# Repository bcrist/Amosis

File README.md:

# Amosis Keyboard

The Amosis is a 40% split keywell board with a Cirque trackpad built into each side.  The case is 3D printed, and features a keywell shape similar to Kinesis or Dactyl keyboards, except with only three rows.

## Controller
This keyboard uses custom controller firmware written from scratch in Zig, and running on an RP2040.

It does not have runtime-swappable layouts or configuration.  Instead, the keyboard layout, layer switching logic, mouse sensitivity, etc. is baked into the firmware, but updating the firmware is just a matter of holding the BOOT button while pressing the RESET button, then dragging a UF2 file to the RPI USB drive.

All of interesting configuration/layout stuff is handed in the [logic.zig](https://github.com/bcrist/Amosis/blob/main/firmware/logic.zig) file.  It should be relatively easy to customize the layout, though if you want to make behavioral changes, you will likely need to know some Zig.

The default layout is based on [Hands Down Gold](https://sites.google.com/alanreiser.com/handsdown#h.j66p50cw2471).  The exact details can be found [here](https://docs.google.com/spreadsheets/d/1Owf2ERAmP1oHp472hNBu8RwOKwRJ6sjyrHRkhDTo6_Y/edit?usp=sharing).

It would probably be possible to use something like QMK with Amosis controllers, but please don't ask me to help with that; I have no interest and little experience with QMK, ZMK, etc.

## Trackpad
Each side of the keyboard integrates a 40mm Cirque GlidePoint trackpad from a Steam Controller.  While Valve stopped producing Steam Controllers years ago, you can still purchase the trackpads from [Mouser](https://www.mouser.com/c/?marcom=118816186), but you will likely need to make some modifications to make this work:

* There are several sizes available; the Steam Controller uses the largest 40mm size (TM40040), but you could use a smaller one if you adjust the case design.
* The retail Circues offer several options for plastic overlays, but the Steam Controller used custom overlays, so you may need to adjust the case design for your chosen overlay style.
* There are (or were) both SPI and I2C versions available.  The Steam Controller only uses SPI, so you'll need to adjust the firmware if you want to use an I2C version (though I think you can change it just by adding/removing a resistor on the Cirque board).  The SPI versions have part numbers TMxx0xx-2024 while the I2C versions have part numbers TMxx0xx-2023.  At time of writing, it appears Mouser no longer carries the I2C version.
* The Steam Controller uses a customized connector pinout that's different than what's documented in the datasheet for the retail version.  You'll need to adjust the schematic board layout to accomodate this.
* An [Alps Haptic Reactor](https://www.mouser.com/ProductDetail/Alps-Alpine/AFT14A903A) force-feedback element is glued to the back of the Steam Controller version and its power is routed through the same FFC cable.  If you buy this separately, you'll have to figure out how you want to connect it to the board.

## Building

Have the controller boards manufactured using the files in the `kicad/gerbers/left/` and `kicad/gerbers/right` folders.

Ensure dependencies are available on your path:
* [Zig](https://ziglang.org/download/)
* [OpenSCAD](https://openscad.org/downloads.html) (2023.03.18 or newer; scroll down to "Development Snapshots")

Adjust the keymapping and layer logic as you like, then run `zig build`.

3D print a case using `zig-out/bin/left.stl` and `zig-out/bin/right.stl`.

Flash the `zig-out/bin/firmware.uf2` and to both controllers (the same file can be used for both sides because the firmware will detect which side it is at boot).

### Wiring
The 3 row signals are driven to 3.3V when scanning a row, and 0V when not scanning that row.
The 7 column signals are read as inputs with weak pull-downs, and treat a high value as indicating that a switch is pressed.
Therefore, there are 2 possible ways to wire the diode/switch matrix that will work:
* Diodes between the row signals and the switches, with a common anode for each row.
* Diodes between the column signals and the switches, with a common cathode for each column.

Note the line on diode packages indicates the cathode side.
Also note while the schematics list a schottky diode part number, any general purpose diodes will work fine for the matrix, e.g. 1N914/1N4148, 1N4001, etc.

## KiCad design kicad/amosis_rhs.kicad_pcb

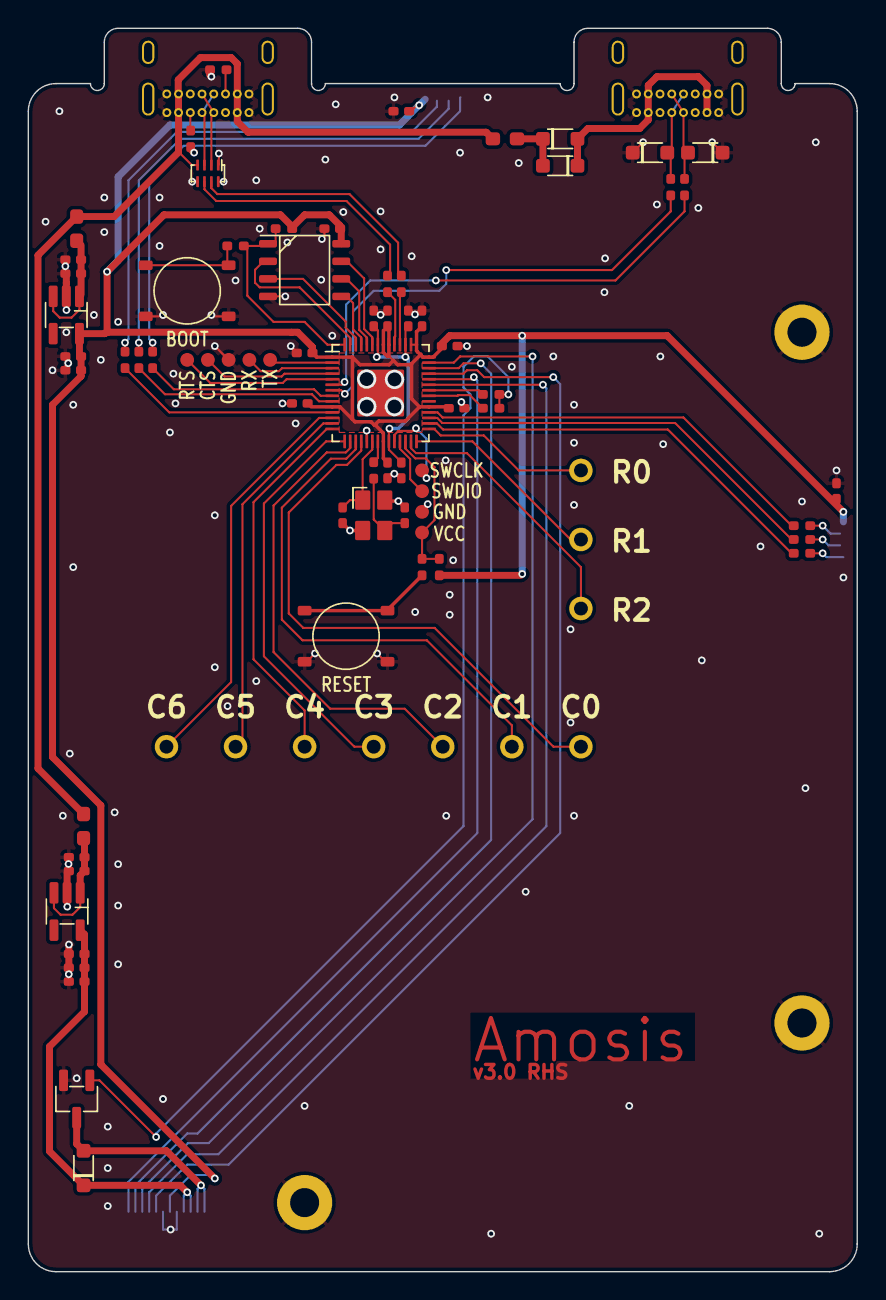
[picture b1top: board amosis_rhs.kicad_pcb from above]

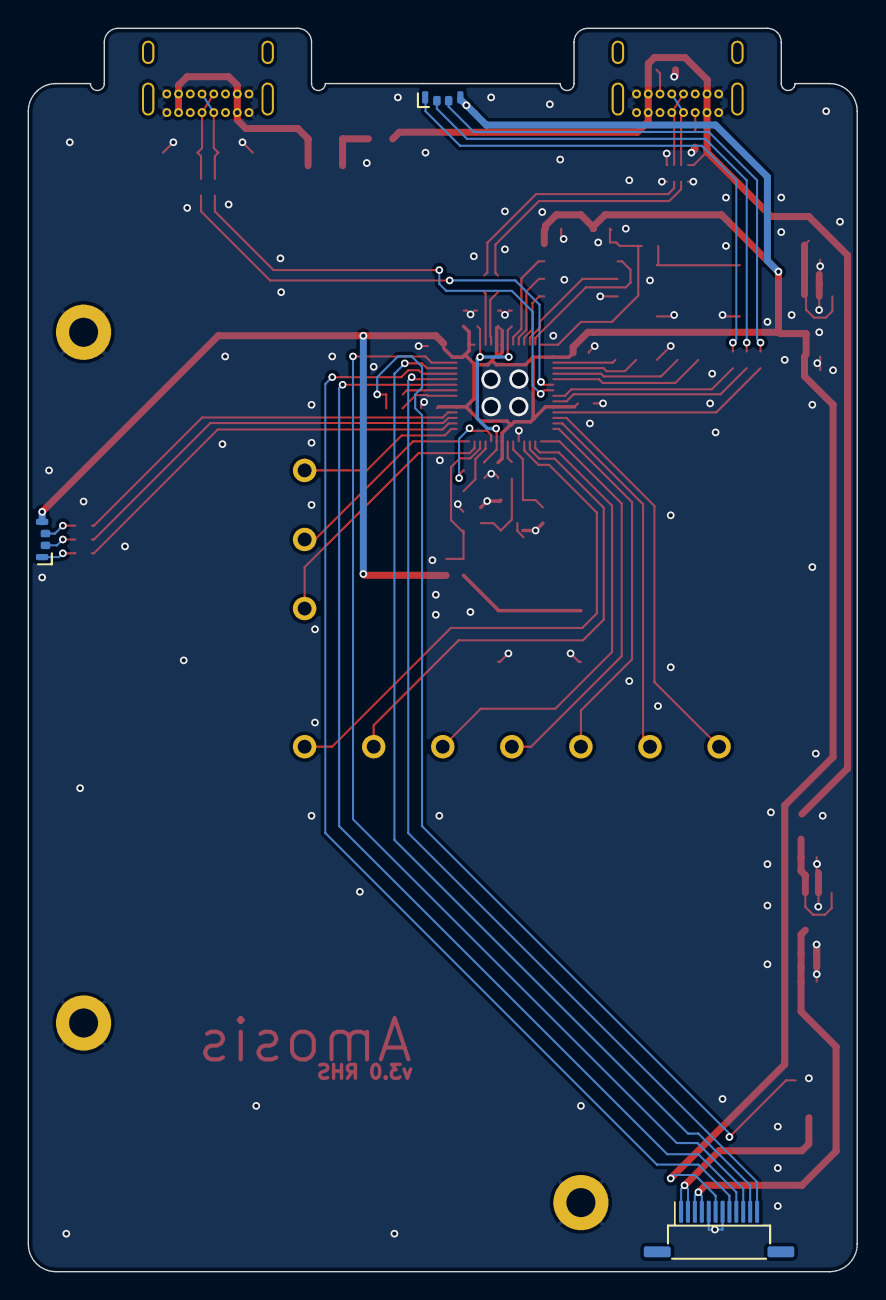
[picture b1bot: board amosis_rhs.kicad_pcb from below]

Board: 2 copper layers, 60.0 x 90.0 mm, 87 parts (5 on the bottom side), 70 nets.

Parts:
C1, C4, C5, C8, C10, C17: 1; C_0402
C2, C3, C6, C7, C11, C12, C13, C14, C15, C16, C18, C19, C20, C23, C24: 0.1; C_0402
C9: 10; C_0402
C21, C22: 14p; C_0402
COL_{0}1: COL_{0}; PinHeader_1x01
COL_{1}1: COL_{1}; PinHeader_1x01
COL_{2}1: COL_{2}; PinHeader_1x01
COL_{3}1: COL_{3}; PinHeader_1x01
COL_{4}1: COL_{4}; PinHeader_1x01
COL_{5}1: COL_{5}; PinHeader_1x01
COL_{6}1: ROW_{0}; PinHeader_1x01
D22, D23: CUS520; SOD-323
D24: ECMF02-4CMX8; DFN-8-2.5x1.2-P0.45
D25, D26: DESD5V0U1BA; SOD-323
D27, D28: LED_BGRA; Harvatek-B3233GBR-20
D29: MMBD914LT1; SOD-323
FB1, FB2, FB3: PE-0603FB121ST; L_0603
J1, J2: USB-C-16; USB_GCT_USB4085-FG-A
J3: VALVE; FFC_GCT_FFC2B28-12-G
M1, M2, M3: GND; MountingHole_M2_Pad
Q1: MMBT3904; SOT-23
R1, R13: 10K; R_0402
R2, R12, R16: 1K; R_0402
R3, R4: 50; R_0402
R5, R8: 27.4; R_0402
R6, R7, R18: 5.1K; R_0402
R9, R14: 120; R_0402
R10, R11, R15, R17: 10; R_0402
R19: 2.2K; R_0402
ROW_{0}1: ROW_{1}; PinHeader_1x01
ROW_{1}1: ROW_{2}; PinHeader_1x01
ROW_{2}1: ROW_{3}; PinHeader_1x01
SW22: RESET; SW_CK_PTS526
SW23: BOOT; SW_CK_PTS526
U1: MIC5504-3.3YM5; SOT-23-5
U2: MIC5504-2.5YM5; SOT-23-5
U3: RP2040; QFN-56-EP-7x7-P0.4
U4: ZD25Q80CT; SOP-8-4.9x3.9-P1.27
X1: RH100-12.000-12-1010-X-TR-NS2
tCTS1: CTS; TestPoint
tGND1, tGND2: GND; TestPoint
tRTS1: RTS; TestPoint
tRUN1: VCC; TestPoint
tRX1: RX; TestPoint
tSWCLK1: SWCLK; TestPoint
tSWDIO1: SWDIO; TestPoint
tTX1: TX; TestPoint

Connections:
+2V5: C7.1, C8.1, C9.1, D29.1 (K), J3.3, J3.4, U2.5 (VOUT)
/COL_{0}: COL_{0}1.1, U3.18 (P15)
/COL_{1}: COL_{1}1.1, U3.17 (P14)
/COL_{2}: COL_{2}1.1, U3.16 (P13)
/COL_{3}: COL_{3}1.1, U3.15 (P12)
/COL_{4}: COL_{4}1.1, U3.14 (P11)
/COL_{5}: COL_{5}1.1, U3.13 (P10)
/COL_{6}: COL_{6}1.1, U3.12 (P9)
/DR: J3.9, U3.37 (P25)
/LINK_RX: R3.2, U3.7 (P5)
/LINK_TX: R4.1, U3.6 (P4)
/MISO: J3.11, U3.40 (P28/A2)
/MOSI: J3.8, U3.39 (P27/A1)
/ROW_{0}: ROW_{0}1.1, U3.29 (P18)
/ROW_{1}: ROW_{1}1.1, U3.28 (P17)
/ROW_{2}: ROW_{2}1.1, U3.27 (P16)
/SCLK: J3.12, U3.38 (P26/A0)
/SS: J3.10, U3.41 (P29/A3)
GND: C1.2, C2.2, C3.2, C4.2, C5.2, C6.2, C7.2, C8.2, C9.2, C10.2, C11.2, C12.2, C13.2, C14.2, C15.2, C16.2, C17.2, C18.2, C19.2, C20.2, C21.2, C22.2, C23.2, C24.2, D24.1, D24.5, D24.8, D25.1 (A1), D26.1 (A1), J1.A1 (GND), J1.A12 (GND), J1.B1 (GND), J1.B12 (GND), J2.A1 (GND), J2.A12 (GND), J2.B1 (GND), J2.B12 (GND), J3.5, J3.7, M1.1, M2.1, M3.1, Q1.2 (E), R6.2, R7.2, SW22.3, SW22.4, SW23.3, SW23.4, U1.2 (GND), U2.2 (GND), U3.19 (GND), U3.EP (GND), U4.4 (GND), X1.2, X1.4, tGND1.1, tGND2.1
unnamed: C22.1, R12.2, X1.3
unnamed: D22.2 (A), D23.1 (K), FB3.2
unnamed: D22.1 (K), D23.2 (A), J1.A4 (V_{BUS}), J1.A9 (V_{BUS}), J1.B4 (V_{BUS}), J1.B9 (V_{BUS})
unnamed: D24.6, R5.2
unnamed: D24.7, R8.1
unnamed: D25.2 (A2), J1.A6 (D+1), J1.B6 (D+2), R3.1
unnamed: D26.2 (A2), J1.A7 (D-1), J1.B7 (D-2), R4.2
unnamed: D27.1 (BK), R9.2
unnamed: D27.2 (GK), R10.2
unnamed: D27.3 (RK), R11.2
unnamed: D28.1 (BK), R14.2
unnamed: D28.2 (GK), R15.2
unnamed: D28.3 (RK), R17.2
unnamed: D29.2 (A), J3.1, J3.2, Q1.3 (C)
unnamed: J2.A5 (CC1), R6.1
unnamed: J2.B5 (CC2), R7.1
unnamed: D24.3, J2.A6 (D+1), J2.B6 (D+2)
unnamed: D24.2, J2.A7 (D-1), J2.B7 (D-2)
unnamed: Q1.1 (B), R18.2, R19.2
unnamed: R2.2, SW22.1, SW22.2
unnamed: R16.2, SW23.1, SW23.2
unnamed: C1.1, C2.1, FB1.2, U1.1 (VIN), U1.3 (EN)
unnamed: C5.1, C6.1, FB2.2, U2.1 (VIN), U2.3 (EN)
unnamed: U3.2 (P0), tTX1.1
unnamed: U3.3 (P1), tRX1.1
unnamed: U3.4 (P2), tCTS1.1
unnamed: U3.5 (P3), tRTS1.1
unnamed: R9.1, U3.8 (P6)
unnamed: R10.1, U3.9 (P7)
unnamed: R11.1, U3.11 (P8)
unnamed: R14.1, U3.30 (P19)
unnamed: R15.1, U3.31 (P20)
unnamed: R17.1, U3.32 (P21)
unnamed: R18.1, U3.35 (P23)
unnamed: R19.1, U3.36 (P24)
unnamed: U3.52 (QSPI_{CLK}), U4.6 (CLK)
unnamed: U3.53 (QSPI_{SD0}), U4.5 (D0)
unnamed: U3.55 (QSPI_{SD1}), U4.2 (D1)
unnamed: U3.54 (QSPI_{SD2}), U4.3 (D2)
unnamed: U3.51 (QSPI_{SD3}), U4.7 (D3)
unnamed: R13.2, R16.1, U3.56 (QSPI_{~SS}), U4.1 (~CS)
unnamed: R1.2, R2.1, U3.26 (RUN), tRUN1.1
unnamed: U3.24 (SWCLK), tSWCLK1.1
unnamed: U3.25 (SWDIO), tSWDIO1.1
unnamed: R5.1, U3.47 (USB_{D+})
unnamed: R8.2, U3.46 (USB_{D-})
unnamed: C17.1, C18.1, C19.1, U3.23 (VDD_{D}), U3.45 (VREG_{OUT}), U3.50 (VDD_{D})
unnamed: C21.1, U3.20 (X_{IN}), X1.1
unnamed: R12.1, U3.21 (X_{OUT})
VBUS: D24.4, FB1.1, FB2.1, FB3.1, J2.A4 (V_{BUS}), J2.A9 (V_{BUS}), J2.B4 (V_{BUS}), J2.B9 (V_{BUS})
VCC: C3.1, C4.1, C10.1, C11.1, C12.1, C13.1, C14.1, C15.1, C16.1, C20.1, C23.1, C24.1, D27.4 (A), D28.4 (A), J3.6, R1.1, R13.1, U1.5 (VOUT), U3.1 (VDD_{IO}), U3.10 (VDD_{IO}), U3.22 (VDD_{IO}), U3.33 (VDD_{IO}), U3.42 (VDD_{IO}), U3.43 (VDD_{ADC}), U3.44 (VREG_{IN}), U3.48 (VDD_{USB}), U3.49 (VDD_{IO}), U4.8 (VCC)

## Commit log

2024-08-17 v3 (WIP)
2024-08-17 fix firmware
2024-08-19 v3 lhs/rhs consolidation
2024-08-27 logic & fixes
2024-08-27 Don't allow changing host location to a side that's not currently connected
2024-08-27 Fix potential hang due to HID input report FIFO overflow
2024-08-27 readme update
2024-08-27 Swap shift and Ctrl to avoid slowdowns for capital T
